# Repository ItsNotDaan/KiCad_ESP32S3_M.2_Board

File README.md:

## **NOTE**: The latest version of this project can be found in the main LiberBoard Repo: https://github.com/ItsNotDaan/LiberBoard/tree/main/Main_Boards/LiBo_M.2_ESP32S3

## ESP32-S3, M.2 based System on Module (SOM)

This is my first KiCad project, developed over the last 2 months alongside my EPS project and work. 

[KiCanvas Webpreview of latest version](https://kicanvas.org/?github=https%3A%2F%2Fgithub.com%2FItsNotDaan%2FKiCad_ESP32S3_M.2_Board%2Ftree%2Fmain%2FESP32S3_M.2_Board)

### Main Components

- **CPU:** ESP32-S3R8
- **Flash:** W25Q16JVUXIQ (16MBIT)
- **Crystals:** 40MHz and 32.768KHz (HSE/LSE)
- **Power/Flashing/Debugging:** USB-C
- **Buck Converter:** TLV62568DBV
- **Buttons:** Two buttons for RESET and BOOT
- **Antenna:** Antenna with PI filter
- **PCB:** 4-layer PCB (Top, GND, VCC, Bottom), internal planes are hidden

All these components are included on a M.2-B-Key footprint. 

### Inspiration

The idea originated from a desire to create a more complex and smaller PCB that incorporates an expensive CPU. This CPU should be versatile enough to be used on different projects. After watching a video from Phil's Lab, I learned that M.2 was a great alternative to the mostly used header pin setup. 

### Future Plans

The ESP32-S3 is not high-end or anything special, but I plan to quickly redesign this board using the newly announced ESP32-P4. It is a really interesting and high-speed CPU based on the RISC-V architecture and I'm excited to start creating some (DSP) code with it. 

I have ordered the components and the PCB to start experimenting with it.

https://www.linkedin.com/in/daan-heetkamp/

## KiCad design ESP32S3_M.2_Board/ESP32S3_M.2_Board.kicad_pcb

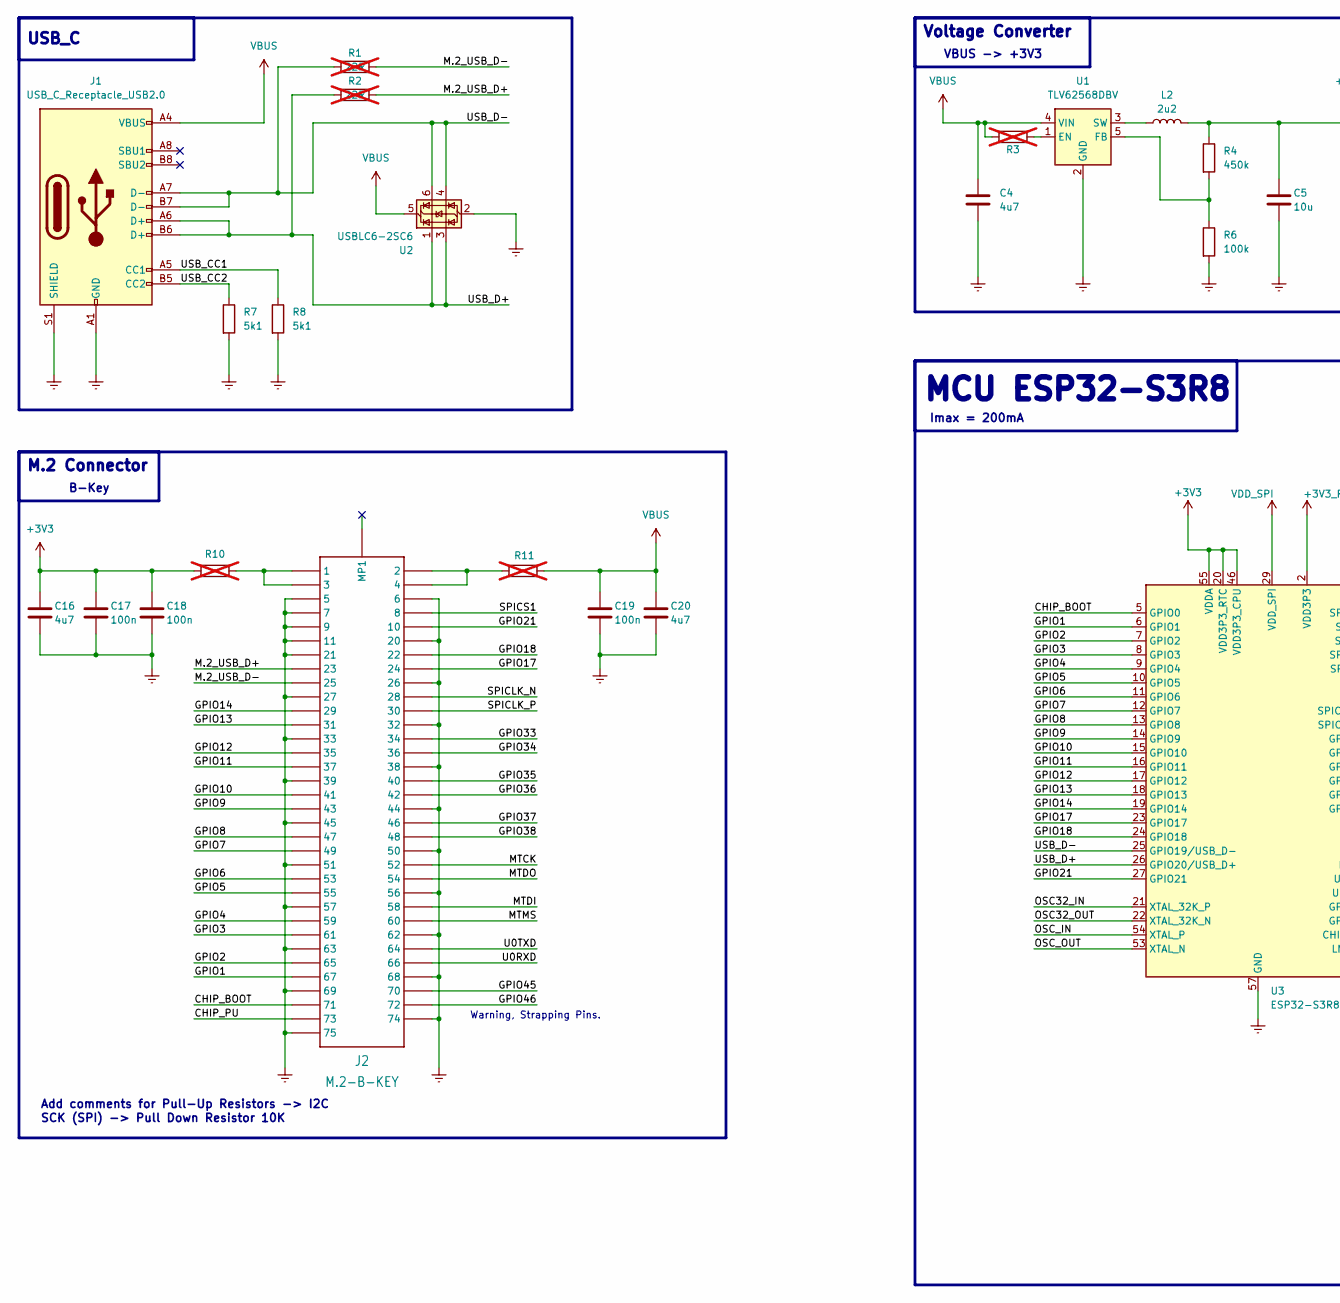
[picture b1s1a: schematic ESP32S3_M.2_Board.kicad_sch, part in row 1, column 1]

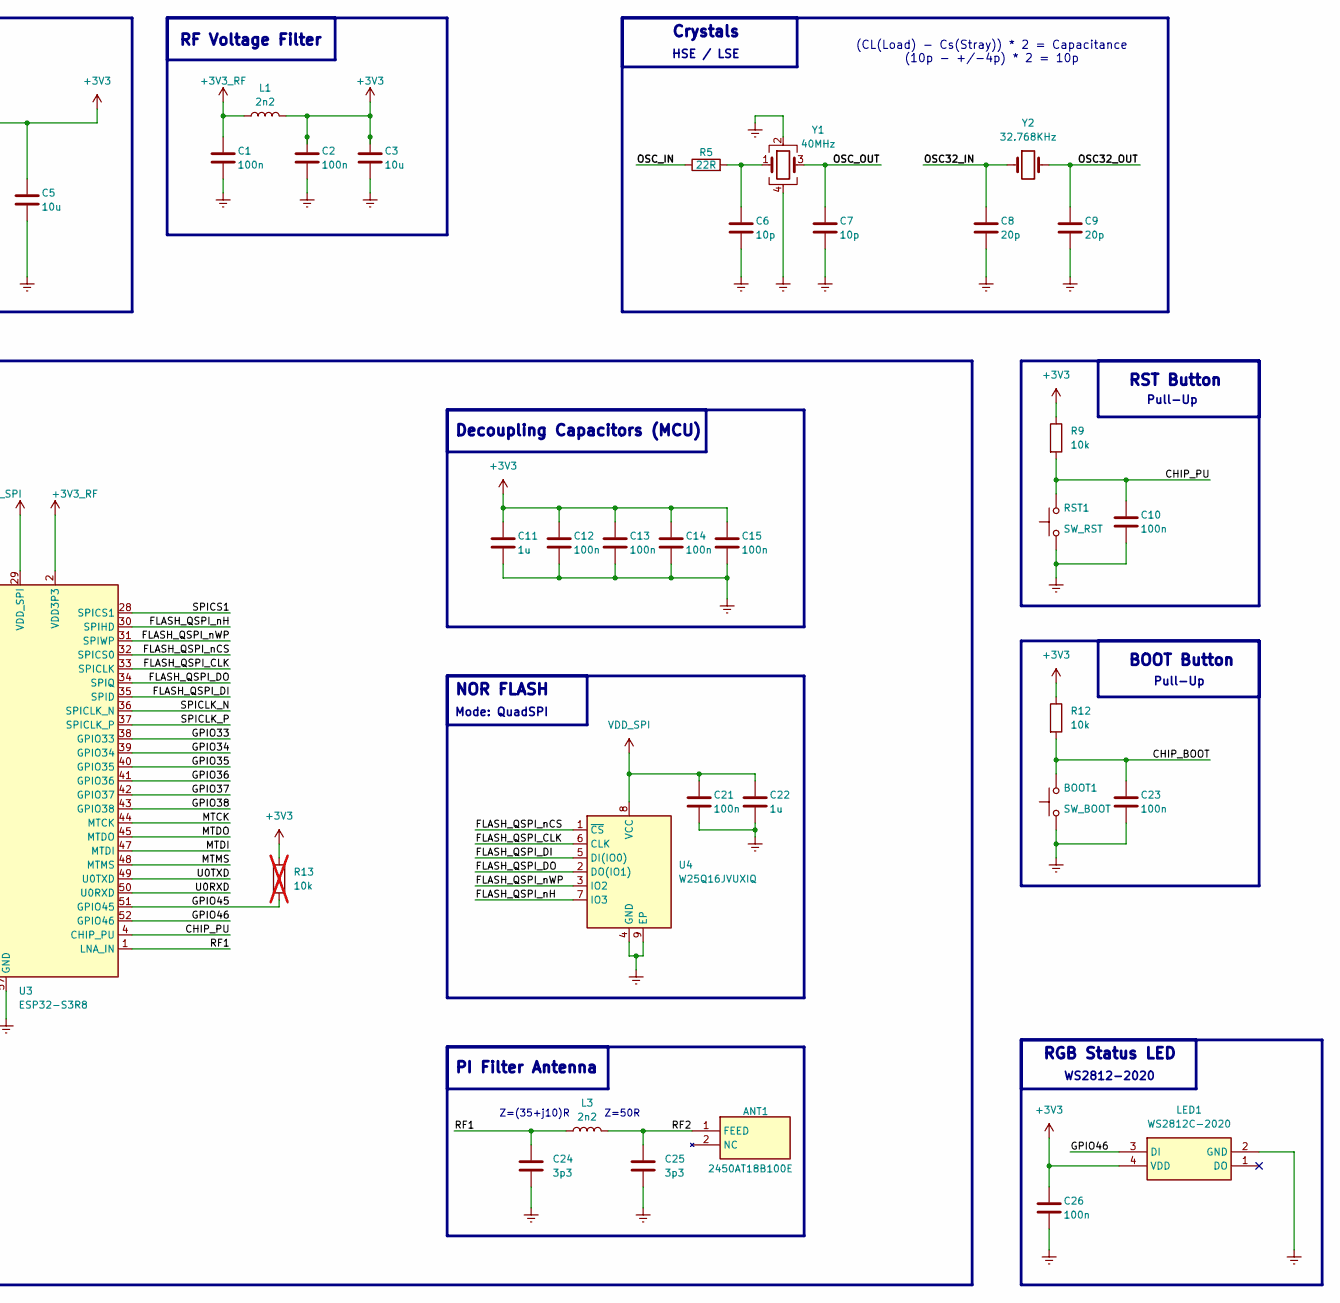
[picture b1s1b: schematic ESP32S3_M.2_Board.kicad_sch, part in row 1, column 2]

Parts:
ANT1: 2450AT18B100E; ANTC3216X140N; Manufacturer_Part_Number 2450AT18B100E
BOOT1: SW_BOOT; SW_SPST_EVQP2
C1, C2, C10, C12, C13, C14, C15, C17, C18, C19, C21, C23, C26: 100n; C_0402_1005Metric_Pad0.74x0.62mm_HandSolder
C3, C5: 10u; C_0402_1005Metric_Pad0.74x0.62mm_HandSolder
C4, C16, C20: 4u7; C_0402_1005Metric_Pad0.74x0.62mm_HandSolder
C6, C7: 10p; C_0402_1005Metric_Pad0.74x0.62mm_HandSolder
C8, C9: 20p; C_0402_1005Metric_Pad0.74x0.62mm_HandSolder
C11, C22: 1u; C_0402_1005Metric_Pad0.74x0.62mm_HandSolder
C24, C25: 3p3; C_0603_1608Metric_Pad1.08x0.95mm_HandSolder
J1: USB_C_Receptacle_USB2.0; USB_C_Receptacle_GCT_USB4105-xx-A_16P_TopMnt_Horizontal
J2: M.2-B-KEY
L1, L3: 2n2; L_0603_1608Metric_Pad1.05x0.95mm_HandSolder
L2: 2u2; L_Wurth_WE-LQSH-4020
LED1: WS2812C-2020; WS2812C2020; Manufacturer_Part_Number WS2812C-2020
R1, R2: 22R; R_0201_0603Metric; not fitted
R3, R13: 10k; R_0201_0603Metric_Pad0.64x0.40mm_HandSolder; not fitted
R4: 450k; R_0402_1005Metric_Pad0.72x0.64mm_HandSolder
R5: 22R; R_0402_1005Metric_Pad0.72x0.64mm_HandSolder
R6: 100k; R_0402_1005Metric_Pad0.72x0.64mm_HandSolder
R7, R8: 5k1; R_0402_1005Metric_Pad0.72x0.64mm_HandSolder
R9, R12: 10k; R_0402_1005Metric_Pad0.72x0.64mm_HandSolder
R10, R11: 10k; R_0402_1005Metric_Pad0.72x0.64mm_HandSolder; not fitted
RST1: SW_RST; SW_SPST_EVQP2
U1: TLV62568DBV; SOT-23-5
U2: USBLC6-2SC6; SOT-23-6
U3: ESP32-S3R8; QFN-56-1EP_7x7mm_P0.4mm_EP4x4mm
U4: W25Q16JVUXIQ; USON-8-2X3_P0.6mm
Y1: 40MHz; Crystal_SMD_3225-4Pin_3.2x2.5mm
Y2: 32.768KHz; Crystal_SMD_3215-2Pin_3.2x1.5mm

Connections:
+3V3: C2.1, C3.1, C5.1, C11.1, C12.1, C13.1, C14.1, C15.1, C16.1, C17.1, C18.1, C26.1, L1.2, L2.2, LED1.4 (VDD), R4.1, R9.1, R10.1, R12.1, R13.1, U3.20 (VDD3P3_RTC), U3.46 (VDD3P3_CPU), U3.55 (VDDA), U3.56 (VDDA); also elsewhere on the board
+3V3_RF: C1.1, L1.1, U3.2 (VDD3P3), U3.3 (VDD3P3)
/CHIP_BOOT: BOOT1.2, C23.1, J2.P$71 (71), R12.2, U3.5 (GPIO0); also elsewhere on the board
/CHIP_PU: C10.1, J2.P$73 (73), R9.2, RST1.2, U3.4 (CHIP_PU); also elsewhere on the board
/FLASH_QSPI_CLK: U3.33 (SPICLK), U4.6 (CLK)
/FLASH_QSPI_DI: U3.35 (SPID), U4.5 (DI(IO0))
/FLASH_QSPI_DO: U3.34 (SPIQ), U4.2 (DO(IO1))
/FLASH_QSPI_nCS: U3.32 (SPICS0), U4.1 (~CS)
/FLASH_QSPI_nH: U3.30 (SPIHD), U4.7 (IO3)
/FLASH_QSPI_nWP: U3.31 (SPIWP), U4.3 (IO2)
/GPIO1: J2.P$67 (67), U3.6 (GPIO1)
/GPIO2: J2.P$65 (65), U3.7 (GPIO2)
/GPIO3: J2.P$61 (61), U3.8 (GPIO3)
/GPIO4: J2.P$59 (59), U3.9 (GPIO4)
/GPIO5: J2.P$55 (55), U3.10 (GPIO5)
/GPIO6: J2.P$53 (53), U3.11 (GPIO6)
/GPIO7: J2.P$49 (49), U3.12 (GPIO7)
/GPIO8: J2.P$47 (47), U3.13 (GPIO8)
/GPIO9: J2.P$43 (43), U3.14 (GPIO9)
/GPIO10: J2.P$41 (41), U3.15 (GPIO10)
/GPIO11: J2.P$37 (37), U3.16 (GPIO11)
/GPIO12: J2.P$35 (35), U3.17 (GPIO12)
/GPIO13: J2.P$31 (31), U3.18 (GPIO13)
/GPIO14: J2.P$29 (29), U3.19 (GPIO14)
/GPIO17: J2.P$24 (24), U3.23 (GPIO17)
/GPIO18: J2.P$22 (22), U3.24 (GPIO18)
/GPIO21: J2.P$10 (10), U3.27 (GPIO21)
/GPIO33: J2.P$34 (34), U3.38 (GPIO33)
/GPIO34: J2.P$36 (36), U3.39 (GPIO34)
/GPIO35: J2.P$40 (40), U3.40 (GPIO35)
/GPIO36: J2.P$42 (42), U3.41 (GPIO36)
/GPIO37: J2.P$46 (46), U3.42 (GPIO37)
/GPIO38: J2.P$48 (48), U3.43 (GPIO38)
/GPIO45: J2.P$70 (70), R13.2, U3.51 (GPIO45)
/GPIO46: J2.P$72 (72), LED1.3 (DI), U3.52 (GPIO46); also elsewhere on the board
/M.2_USB_D+: J2.P$23 (23), R2.2
/M.2_USB_D-: J2.P$25 (25), R1.2
/MTCK: J2.P$52 (52), U3.44 (MTCK)
/MTDI: J2.P$58 (58), U3.47 (MTDI)
/MTDO: J2.P$54 (54), U3.45 (MTDO)
/MTMS: J2.P$60 (60), U3.48 (MTMS)
/OSC32_IN: C8.1, U3.21 (XTAL_32K_P), Y2.1
/OSC32_OUT: C9.1, U3.22 (XTAL_32K_N), Y2.2
/OSC_IN: R5.1, U3.54 (XTAL_P)
/OSC_OUT: C7.1, U3.53 (XTAL_N), Y1.3
/RF1: C24.1, L3.1, U3.1 (LNA_IN)
/RF2: ANT1.1 (FEED), C25.1, L3.2
/SPICLK_N: J2.P$28 (28), U3.36 (SPICLK_N)
/SPICLK_P: J2.P$30 (30), U3.37 (SPICLK_P)
/SPICS1: J2.P$8 (8), U3.28 (SPICS1)
/U0RXD: J2.P$66 (66), U3.50 (U0RXD)
/U0TXD: J2.P$64 (64), U3.49 (U0TXD)
/USB_CC1: J1.A5 (CC1), R8.1
/USB_CC2: J1.B5 (CC2), R7.1
/USB_D+: J1.A6 (D+), J1.B6 (D+), R2.1, U2.1 (I/O1), U2.3 (I/O2), U3.26 (GPIO20/USB_D+)
/USB_D-: J1.A7 (D-), J1.B7 (D-), R1.1, U2.4 (I/O2), U2.6 (I/O1), U3.25 (GPIO19/USB_D-)
Earth: BOOT1.1, C1.2, C2.2, C3.2, C4.2, C5.2, C6.2, C7.2, C8.2, C9.2, C10.2, C11.2, C12.2, C13.2, C14.2, C15.2, C16.2, C17.2, C18.2, C19.2, C20.2, C21.2, C22.2, C23.2, C24.2, C25.2, C26.2, J1.A1 (GND), J1.A12 (GND), J1.B1 (GND), J1.B12 (GND), J1.S1 (SHIELD), J2.P$5 (5), J2.P$6 (6), J2.P$7 (7), J2.P$9 (9), J2.P$11 (11), J2.P$20 (20), J2.P$21 (21), J2.P$26 (26), J2.P$27 (27), J2.P$32 (32), J2.P$33 (33), J2.P$38 (38), J2.P$39 (39), J2.P$44 (44), J2.P$45 (45), J2.P$50 (50), J2.P$51 (51), J2.P$56 (56), J2.P$57 (57), J2.P$62 (62), J2.P$63 (63), J2.P$68 (68), J2.P$69 (69), J2.P$74 (74), J2.P$75 (75), LED1.2 (GND), R6.2, R7.2, R8.2, RST1.1, U1.2 (GND), U2.2 (GND), U3.57 (GND), U4.4 (GND), U4.9 (EP), Y1.2, Y1.4; also elsewhere on the board
unnamed: C6.1, R5.2, Y1.1
unnamed: J2.P$1 (1), J2.P$3 (3), R10.2
unnamed: J2.P$2 (2), J2.P$4 (4), R11.1
unnamed: R3.2, U1.1 (EN)
unnamed: R4.2, R6.1, U1.5 (FB)
unnamed: L2.1, U1.3 (SW)
VBUS: C4.1, C19.1, C20.1, J1.A4 (VBUS), J1.A9 (VBUS), J1.B4 (VBUS), J1.B9 (VBUS), R3.1, R11.2, U1.4 (VIN), U2.5 (VBUS)
VDD_SPI: C21.1, C22.1, U3.29 (VDD_SPI), U4.8 (VCC)

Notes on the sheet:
RGB Status LED
BOOT Button
Crystals
B-Key
HSE / LSE
Add comments for Pull-Up Resistors -> I2C
Voltage Converter
MCU ESP32-S3R8
RF Voltage Filter
Mode: QuadSPI
NOR FLASH
USB_C
SCK (SPI) -> Pull Down Resistor 10K
M.2 Connector
RST Button
WS2812-2020
Decoupling Capacitors (MCU)
Pull-Up
Warning, Strapping Pins.
VBUS -> +3V3
Z=(35+j10)R
PI Filter Antenna
(CL(Load) - Cs(Stray)) * 2 = Capacitance (10p - +/-4p) * 2 = 10p
Imax = 200mA
Z=50R

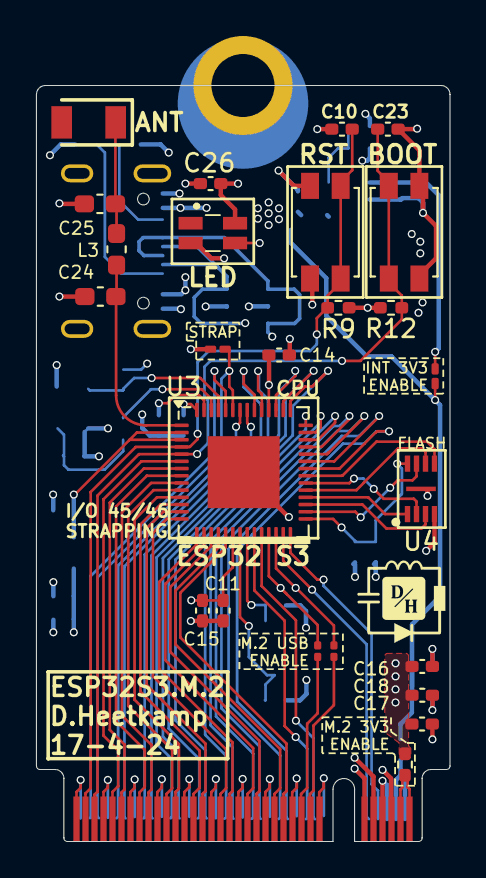
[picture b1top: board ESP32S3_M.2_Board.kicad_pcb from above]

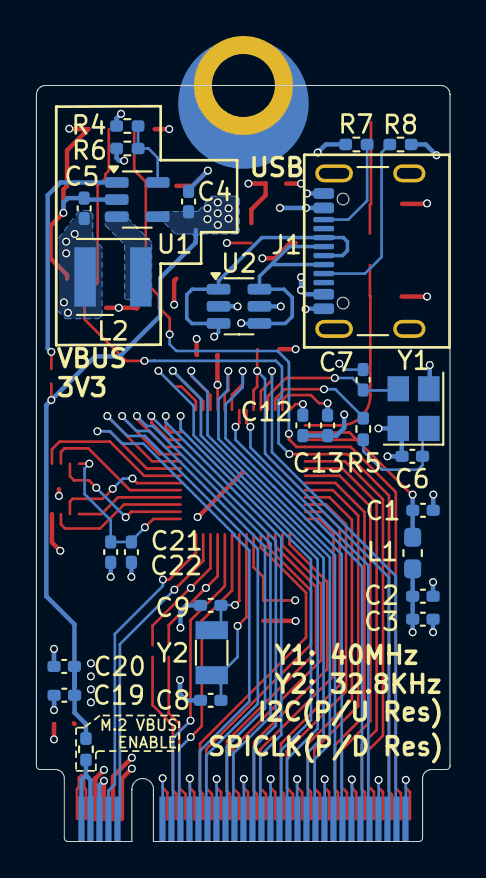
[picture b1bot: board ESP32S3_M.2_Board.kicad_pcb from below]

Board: 4 copper layers, 23.0 x 42.0 mm, 54 parts (28 on the bottom side), 65 nets.

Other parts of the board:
BOOT: SW_BOOT; SW_SPST_EVQP2
LED: WS2812C-2020; WS2812C2020
RST: SW_RST; SW_SPST_EVQP2

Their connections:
+3V3: LED.4 (VDD); also elsewhere on the board
/CHIP_BOOT: BOOT.2; also elsewhere on the board
/CHIP_PU: RST.2; also elsewhere on the board
/GPIO46: LED.3 (DI); also elsewhere on the board
Earth: BOOT.1, LED.2 (GND), RST.1; also elsewhere on the board

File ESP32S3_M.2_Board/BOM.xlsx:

Designator | Footprint | Quantity | Comment | Supplier and ref
Y2 | Crystal_SMD_3215-2Pin_3.2x1.5mm | 1 | 32.768KHz
L2 | L_Wurth_WE-LQSH-4020 | 1 | 2u2
U4 | USON-8-2X3_P0.6mm | 1 | W25Q16JVUXIQ
LED | WS2812C2020 | 1 | WS2812C-2020
ANT1 | ANTC3216X140N | 1 | 2450AT18B100E
C9,C8 | C_0402_1005Metric_Pad0.74x0.62mm_HandSolder | 2 | 20p
C21,C13,C1,C19,C12,C2,C23,C10,C18,C17,C15,C26,C14 | C_0402_1005Metric_Pad0.74x0.62mm_HandSolder | 13 | 100n
J1 | USB_C_Receptacle_GCT_USB4105-xx-A_16P_TopMnt_Horizontal | 1 | USB_C_Receptacle_USB2.0
C6,C7 | C_0402_1005Metric_Pad0.74x0.62mm_HandSolder | 2 | 10p
R7,R8 | R_0402_1005Metric_Pad0.72x0.64mm_HandSolder | 2 | 5k1
R5 | R_0402_1005Metric_Pad0.72x0.64mm_HandSolder | 1 | 22R
C3,C5 | C_0402_1005Metric_Pad0.74x0.62mm_HandSolder | 2 | 10u
U2 | SOT-23-6 | 1 | USBLC6-2SC6
R4 | R_0402_1005Metric_Pad0.72x0.64mm_HandSolder | 1 | 450k
C4,C20,C16 | C_0402_1005Metric_Pad0.74x0.62mm_HandSolder | 3 | 4u7
Y1 | Crystal_SMD_3225-4Pin_3.2x2.5mm | 1 | 40MHz
L1,L3 | L_0603_1608Metric_Pad1.05x0.95mm_HandSolder | 2 | 2n2
C22,C11 | C_0402_1005Metric_Pad0.74x0.62mm_HandSolder | 2 | 1u
R6 | R_0402_1005Metric_Pad0.72x0.64mm_HandSolder | 1 | 100k
U1 | SOT-23-5 | 1 | TLV62568DBV
BOOT | SW_SPST_EVQP2 | 1 | SW_BOOT
R9,R12 | R_0402_1005Metric_Pad0.72x0.64mm_HandSolder | 2 | 10k
J2 | M.2-B-KEY | 1 | M.2-B-KEY
C24,C25 | C_0603_1608Metric_Pad1.08x0.95mm_HandSolder | 2 | 3p3
RST | SW_SPST_EVQP2 | 1 | SW_RST
U3 | QFN-56-1EP_7x7mm_P0.4mm_EP4x4mm | 1 | ESP32-S3R8

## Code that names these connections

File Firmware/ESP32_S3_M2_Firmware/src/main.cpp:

#include <Arduino.h>
#include <LED.h>

/*To do:
  - Add the SPI flash memory. 
  - Add the RGB LED.
  - Check the USB connection.
  - Add some DSP functions in Espressif IoT Development Framework.
  - Add a WiFi connection.
  - Add a Bluetooth connection.

*/

void setup() {
  // put your setup code here, to run once:
  
  //Init LED
  FastLED.addLeds<LED_TYPE, DATA_PIN, COLOR_ORDER>(leds, NUM_LEDS);
}

void loop() {
  // put your main code here, to run repeatedly:
  RGB_LED(true, 255, 0, 0);
  delay(1000);
  RGB_LED(false, 0, 0, 0);
  delay(1000);
}

// ESP32S3 PINS	ESP32S3 PIN_FUNCT	USED_PINS	M.2_USED_PINS	EXTRA_INFORMATION
// 1	LNA_IN	-	-	-
// 2	VDD3P3	-	-	-
// 3	VDD3P3	-	-	-
// 4	CHIP_PU	CHIP_PU	73	-
// 5	GPIO0	CHIP_BOOT	71	-
// 6	GPIO1	GPIO1	67	-
// 7	GPIO2	GPIO2	65	-
// 8	GPIO3	GPIO3	61	-
// 9	GPIO4	GPIO4	59	-
// 10	GPIO5	GPIO5	55	-
// 11	GPIO6	GPIO6	53	-
// 12	GPIO7	GPIO7	49	-
// 13	GPIO8	GPIO8	47	-
// 14	GPIO9	GPIO9	43	-
// 15	GPIO10	GPIO10	41	-
// 16	GPIO11	GPIO11	37	-
// 17	GPIO12	GPIO12	35	-
// 18	GPIO13	GPIO13	31	-
// 19	GPIO14	GPIO14	29	-
// 20	VDD3P3_RTC	-	-	-
// 21	XTAL_32K_P	-	-	-
// 22	XTAL_32K_N	-	-	-
// 23	GPIO17	GPIO17	24	-
// 24	GPIO18	GPIO18	22	-
// 25	GPIO19/USB_D-	USB_D-	25	Solder_Pad
// 26	GPIO20/USB_D+	USB_D+	23	Solder_Pad
// 27	GPIO21	GPIO21	10	-
// 28	SPICS1	SPICS1	8	-
// 29	VDD_SPI	-	-	-
// 30	SPIHD	-	-	-
// 31	SPIWP	-	-	-
// 32	SPICS0	-	-	-
// 33	SPICLK	-	-	-
// 34	SPIQ	-	-	-
// 35	SPID	-	-	-
// 36	SPICLK_N	SPICLK_N	28	-
// 37	SPICLK_P	SPICLK_P	30	-
// 38	GPIO33	GPIO33	34	-
// 39	GPIO34	GPIO34	36	-
// 40	GPIO35	GPIO35	40	-
// 41	GPIO36	GPIO36	42	-
// 42	GPIO37	GPIO37	46	-
// 43	GPIO38	GPIO38	48	-
// 44	MTCK	MTCK	53	-
// 45	MTDO	MTDO	54	-
// 46	VDD3P3_CPU	-	-	-
// 47	MTDI	MTDI	58	-
// 48	MTMS	MTMS	60	-
// 49	U0TXD	U0TXD	64	-
// 50	U0RXD	U0RXD	66	-
// 51	GPIO45	GPIO45	70	Pull_Up_Res/Strapping Pins
// 52	GPIO46	GPIO46	72	RGB_LED
// 53	XTAL_N	-	-	-
// 54	XTAL_P	-	-	-
// 55	VDDA	-	-	-
// 56	VDDA	-	-	-
// 57	GND	-	-	-

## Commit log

2024-04-24 feat: full push
2024-04-24 feat: changed the readme
2024-04-24 fix: points
2024-04-24 Removed unneccesary things
2024-05-08 Firmware Adding
2025-03-01 feat: push for v.2
2025-12-21 Update README with link to main LiberBoard Repo
    Added a note about the latest version of the project.
